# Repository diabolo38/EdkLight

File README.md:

Aim is to Drive my ebike light using the edk display light control via "+" key that is sent to motor via uart. 
optionaly brake light can be added  if conecting in at the higo 8 1 to 4 side.

An small mcu board stm32f103c6t6/c8t6  snif the edk-101  uart  and will enable power to light via  gpio base on control motor info snifed  
see https://github.com/hurzhurz/tsdz2/blob/master/serial-communication.md#motor-status-flags 

Hardware
---------
- Julet/Higo M8 5 pin Y spliter (light only) or Higo 8 extension for brake addition,  
- Julet 5 pin connector with 30cm wire take care that wires color don't seam to folow any standard (try conection and probe before to plug)
- 5V  step down  regulator with high enougth input voltage (54V + for 500W 48V TDS2B ) to feed 5V power from 48V bat line 
- MosFet  to drive  light pwoer (any mos capable to drive 500mA to 1A with  VDS max > 54V  ) 
- few discrete (zener, resistor)

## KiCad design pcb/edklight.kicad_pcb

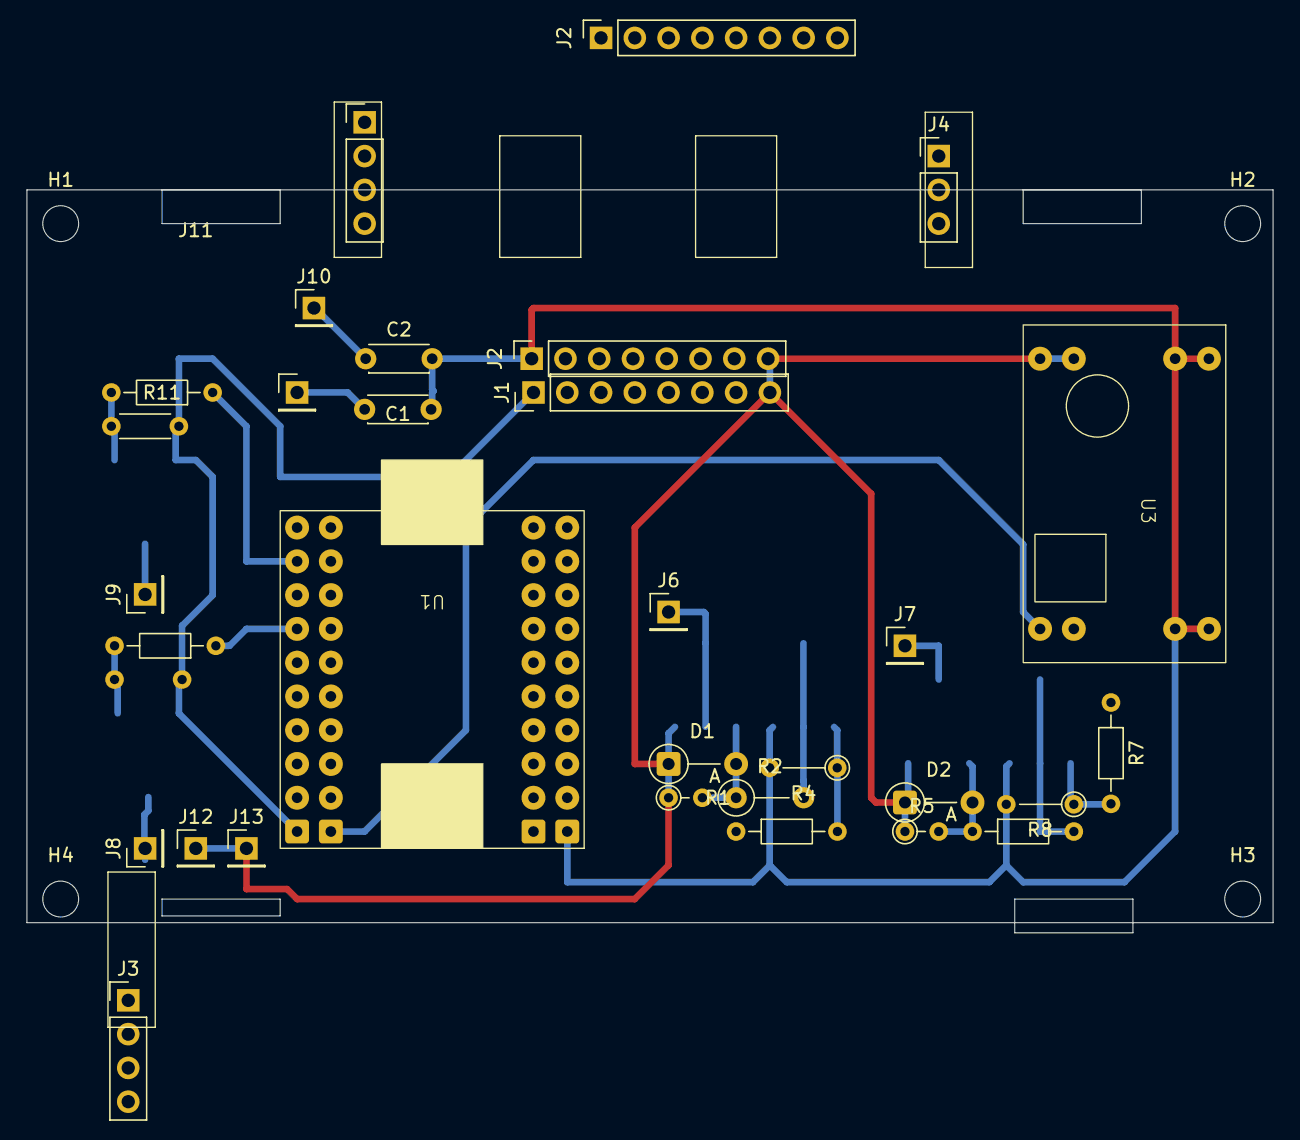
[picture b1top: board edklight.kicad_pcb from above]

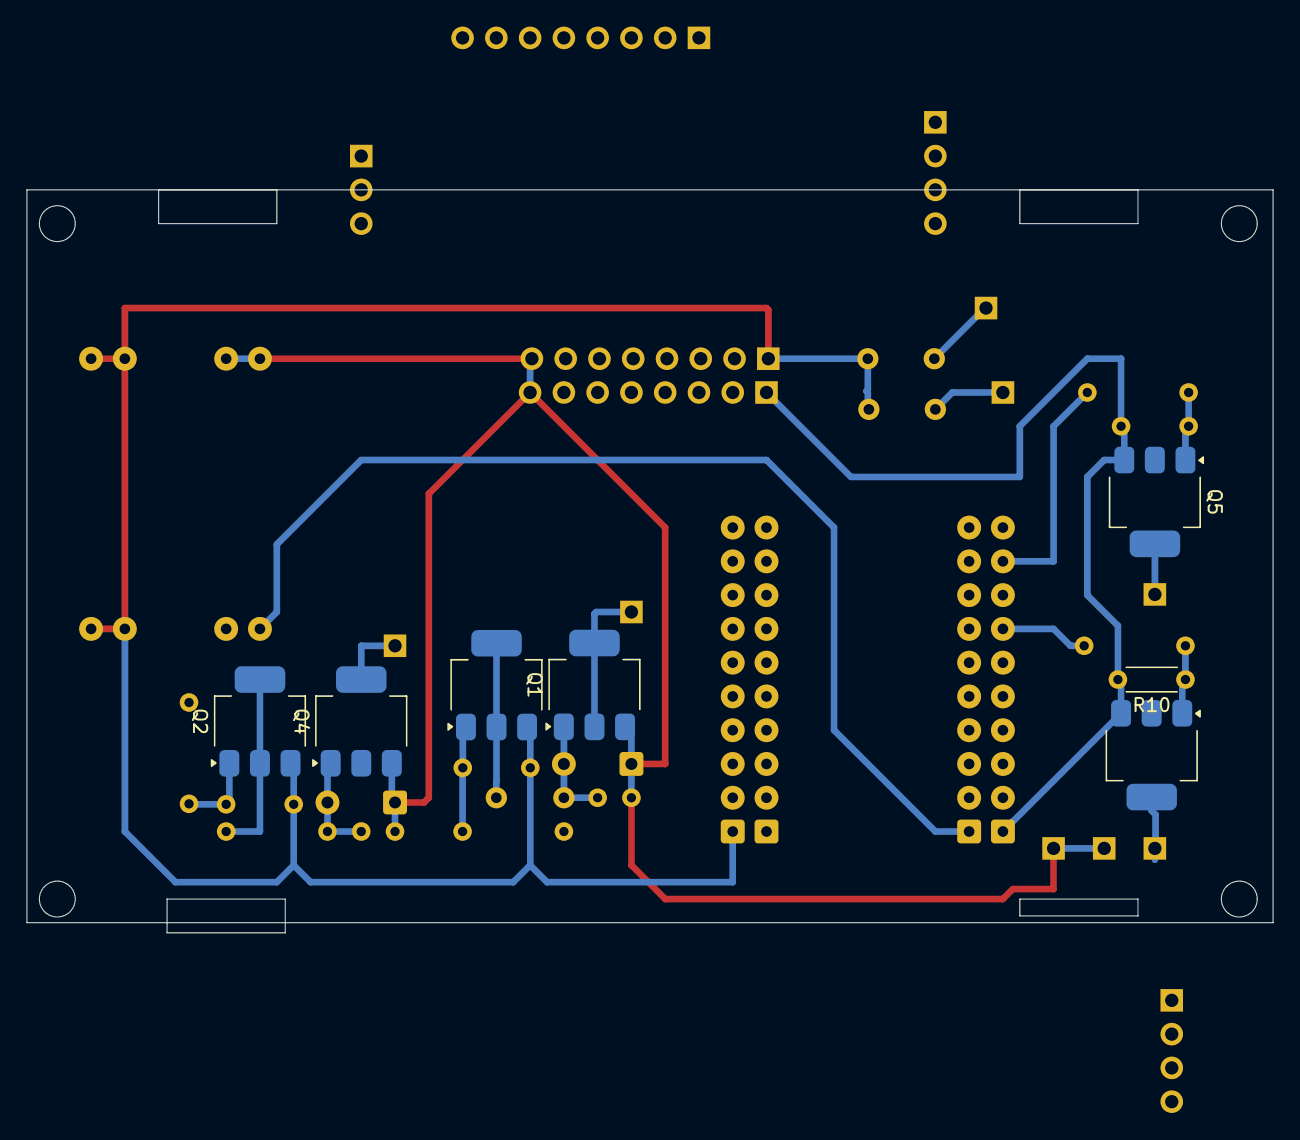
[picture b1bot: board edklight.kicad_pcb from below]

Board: 2 copper layers, 93.7 x 55.9 mm, 42 parts (7 on the bottom side), 27 nets.

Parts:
C1, C2: 100n; C_Disc_D4.3mm_W1.9mm_P5.00mm
D1, D2: 15V; D_A-405_P5.08mm_Vertical_AnodeUp
H1, H2, H3, H4: MountingHole; MountingHole_2.7mm_M2.5_DIN965
J1: MotorIn; PinHeader_1x08_P2.54mm_Vertical
J2, J2#2: ToLcd; PinSocket_1x08_P2.54mm_Vertical
J3: RearLight; PinHeader_1x04_P2.54mm_Vertical
J4: Fr Light; PinHeader_1x03_P2.54mm_Vertical
J5: 2 But Ctrl; PinHeader_1x04_P2.54mm_Vertical
J6, J7, J8, J9, J10, J11, J12, J13: Conn_01x01_Pin; PinHeader_1x01_P2.54mm_Vertical
Q1, Q4: ZXMP4A16G; SOT-223-3_TabPin2
Q2, Q3, Q5: nce6005; SOT-223-3_TabPin2
Q6: BSP89; SOT-223-3_TabPin2
R1, R5: 15K; R_Axial_DIN0204_L3.6mm_D1.6mm_P2.54mm_Vertical
R2: 33K; R_Axial_DIN0207_L6.3mm_D2.5mm_P5.08mm_Vertical
R3, R7, R9, R11: 330; R_Axial_DIN0204_L3.6mm_D1.6mm_P7.62mm_Horizontal
R4: 10K; R_Axial_DIN0204_L3.6mm_D1.6mm_P5.08mm_Vertical
R6: 33K; R_Axial_DIN0204_L3.6mm_D1.6mm_P7.62mm_Horizontal
R8: 10k; R_Axial_DIN0204_L3.6mm_D1.6mm_P5.08mm_Vertical
R10, R12: 10k; R_Axial_DIN0204_L3.6mm_D1.6mm_P5.08mm_Horizontal
U1: MiniF103
U3: dce003

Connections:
+5VD: U1.11 (5V), U3.7 (OUT+), U3.8 (OUT+)
BrakeIn: J1.5, J2#2.5, U1.19 (B9)
FLigh: J6.1, Q1.2 (D)
FLighOn: R3.1, U1.22 (B14)
GND: C1.2, C2.2, J1.1, J2#2.1, J5.1, J5.3, Q2.3 (S), Q3.3 (S), Q5.3 (S), Q6.3 (S), R4.2, R8.2, R10.2, R12.2, U1.1 (GND), U1.21 (GND), U3.1 (VIN-), U3.2 (VIN-), U3.5 (OUT-), U3.6 (OUT-)
Horn: J7.1, Q4.2 (D)
HornBut: C1.1, J5.2, J11.1, U1.28 (A5)
HornOn: R7.1, U1.23 (B12)
LighBut: C2.1, J5.4, J10.1, U1.30 (A1)
unnamed: D1.2 (A), Q1.1 (G), R1.2, R2.1
unnamed: D2.2 (A), Q4.1 (G), R5.2, R6.1
unnamed: J1.2, J2#2.2
unnamed: J1.3, J2#2.3
unnamed: J1.7, J2#2.7
unnamed: Q2.2 (D), R6.2
unnamed: Q2.1 (G), R7.2, R8.1
unnamed: Q3.2 (D), R2.2
unnamed: Q3.1 (G), R3.2, R4.1
unnamed: Q5.1 (G), R11.2, R12.1
unnamed: Q6.1 (G), R9.2, R10.1
RBrake: J8.1, Q6.2 (D)
RBrakeOn: R9.1, U1.7 (B5)
RLigh: J9.1, Q5.2 (D)
RLighOn: R11.1, U1.9 (B8)
RX: J1.4, J2#2.4, U1.29 (A3)
TX: J1.6, J2#2.6, U1.34 (B11)
VDD: D1.1 (K), D2.1 (K), J1.8, J2#2.8, J3.2, J3.4, J12.1, J13.1, Q1.3 (S), Q4.3 (S), R1.1, R5.1, U3.3 (VIN+), U3.4 (En)

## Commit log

2026-01-09 initial commit basic rx fn to be tested
2026-01-09 rx tx dbg in progress to regn with correct usart bps
2026-01-09 regen mcu clk to low , debug time out
    likely mcu to slow causing timer/uart races bad behavior
    is now ok 2ms time out maye a bit short 3 ms woumd be better
2026-01-10 led wip, dbg io chg , more notes
2026-01-10 led control debug done
2026-01-12 Mot Rx ok trace debug not working
2026-01-12 faiel to get itm trace , using tx or edk usart for debug motor
2026-01-13 add link for dc dc in notes
2026-01-17 test debg use of tim1 for pwm light diming
2026-01-17 validate front light diming add pwr measure on note
2026-01-17 add kikack proh,sch,pcb and noye about it
2026-01-18 note mcu brd, sch/ lib with BlackPill and Mini F103
2026-01-18 fix pins in mini103 and bp103
2026-01-24 ee data start check and ld rexerved 1kb on top
2026-01-24 notes: higo8 update pinout eiver TZDZ2 dif 2B or info was wrong
2026-01-24 pcb swicth to mini f103 updtae higo ,single pad for wire conection
2026-01-25 md udpate higo8 and brake addition , try chn pwm
    use of timer chn may help moving light to different mcu pin that would
    help pcb routin or proto wiring (no crossing shorter wire)
2026-01-26 migrate cube proj to f103C8 (tweak export + merge dif)
2026-01-26 add button connector info
2026-01-27 pcb : chg button pin add debounce capacitor
2026-01-27 try capacitor value for debounce on exti with inetrnall pull
2026-01-28 pcb : hi side mos wrong siden , chg few R+D footprint
2026-02-04 update doc with wired connector
2026-02-04 pcb change some placement inline with proto + wire con
2026-02-05 regen new i/o pin , brake a0 swap not 5V , new usb uart and usart swap
2026-02-05 regen uart irq enable missing, switch ld to c8 , usb uart cmd wip
2026-02-06 doc rear higo wiring/pinout
2026-02-06 wip usb uartx cmd and log
2026-02-06 no timeout when not rx yet , usb serial cmd debug/log wip
2026-02-08 mov ee + log to new file log+ee test ok, light but lvl lwo active
2026-02-08 refactor task name, erase cmd, brake on non move , light but rework
2026-02-11 split lbut code for easier testability , lbut train 2+3 press detect
2026-02-13 missing new file for button
2026-02-13 extract flight lvl fn, handle ch1 ch2n swap alternative , start powmn
2026-02-13 tune short press time, fix long press , setup cong chg validated
2026-02-13 horn task was not called
2026-02-13 on/off by button long press , high/low beam by short button
2026-02-14 issue in brake debounce logic state not stored
2026-02-14 regen pull up on brake minimize random on if float when motor off
2026-02-14 brake oberhide when steady logic wrong missing time reset when release
2026-02-14 ev but long was generated for normal case
2026-02-14 finished proto pcb image top/down
